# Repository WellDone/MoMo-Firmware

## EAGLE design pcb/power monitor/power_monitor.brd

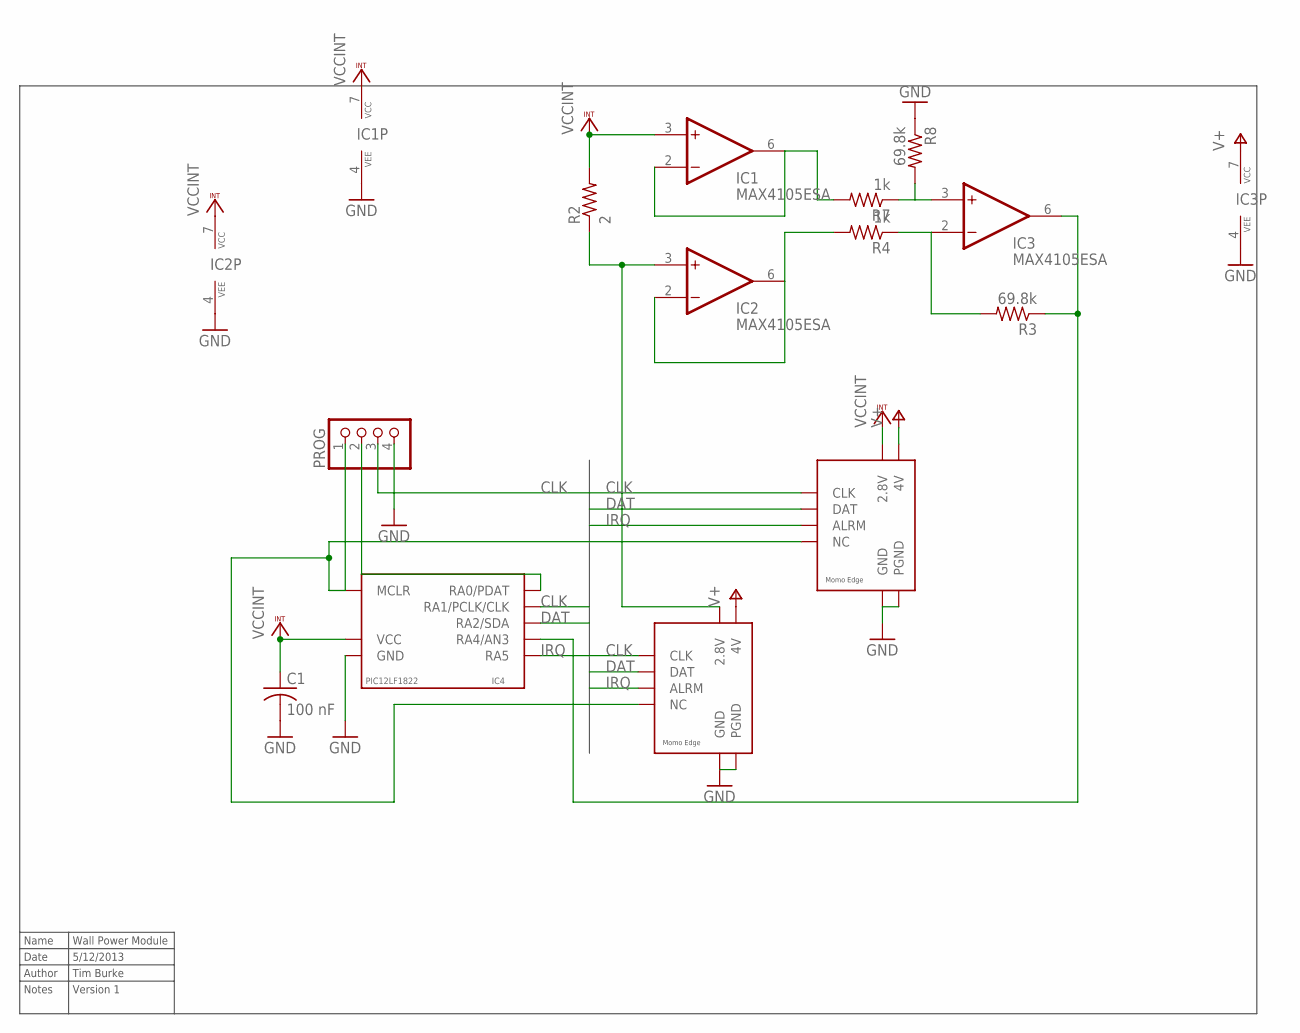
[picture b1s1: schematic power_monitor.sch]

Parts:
C1: 100 nF; C0402
IC1, IC2, IC3: MAX4105ESA; SO08
IC4: PIC12LF1822; SOIC8
PROG: PINHD-1X4; 1X04
R2: 2; R0603
R3, R8: 69.8k; R0603
R4, R7: 1k; R0603
U$6: MOMO-EDGE-8F
U$7: MOMO-EDGE-8M

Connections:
CLK: IC4.6 (RA1/PCLK/CLK), PROG.3, U$6.CLK, U$7.CLK
DAT: IC4.5 (RA2/SDA), U$6.DAT, U$7.DAT
GND: C1.2, IC1.4 (VEE), IC2.4 (VEE), IC3.4 (VEE), IC4.8 (GND), PROG.4, R8.1, U$6.GND, U$6.PGND, U$7.GND, U$7.PGND
IRQ: IC4.2 (RA5), U$6.ARLM (ALRM), U$7.ALRM
unnamed: IC4.4 (MCLR), PROG.1, U$6.NV (NC), U$7.NC
unnamed: IC3.6 (OUT), IC4.3 (RA4/AN3), R3.1
unnamed: IC2.2 (-IN), IC2.6 (OUT), R4.2
unnamed: IC1.2 (-IN), IC1.6 (OUT), R7.2
unnamed: IC3.2 (-IN), R3.2, R4.1
unnamed: IC4.7 (RA0/PDAT), PROG.2
unnamed: IC3.3 (+IN), R7.1, R8.2
unnamed: IC2.3 (+IN), R2.1, U$7.V28 (2.8V)
V+: IC3.7 (VCC), U$6.V4. (4V), U$7.V4 (4V)
VCCINT: C1.1, IC1.3 (+IN), IC1.7 (VCC), IC2.7 (VCC), IC4.1 (VCC), R2.2, U$6.V28 (2.8V)

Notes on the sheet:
Name
Wall Power Module
Date
5/12/2013
Author
Tim Burke
Notes
Version 1

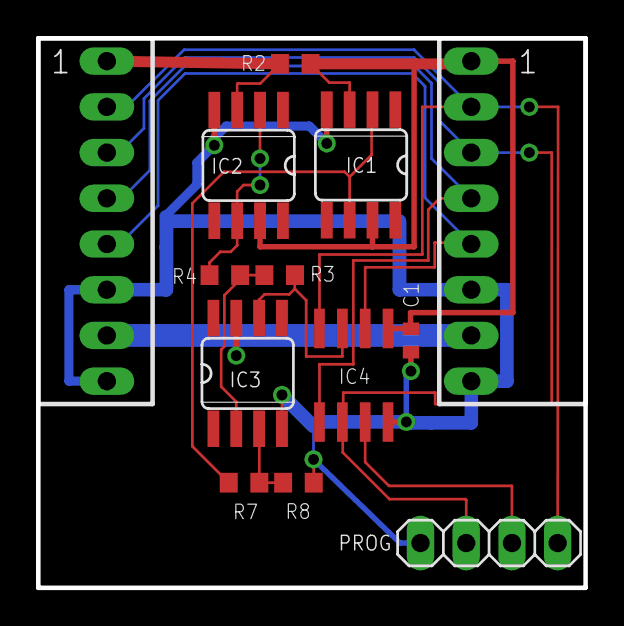
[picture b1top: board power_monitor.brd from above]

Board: 2 copper layers, 30.4 x 30.5 mm, 13 parts (0 on the bottom side), 14 nets.
